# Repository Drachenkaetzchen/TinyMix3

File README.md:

# TinyMix3

TinyMix3 is a very small, 3 channel stereo audio mixer for your pocket. It features touch and USB control and is meant
to be powered by USB. 

## Features

- Very low power consumption (<50mA). Can be powered by an USB Power Bank
- USB powered
- Touch control
- USB control (presented as serial interface to the host)

## Purpose

You can use TinyMix3 to:

- Automate 3 channel stereo mixing
- Mix 3 stereo channels on the go, ideal for musicians who don't want to carry around bulky mixers

## Usage

Manual mixing

- Connect your inputs and your output
- Touch the "CH" button to switch between the three input channels. The selected channel is indicated via the LEDs.
- After a second, TinyMix3 indicates the volume for the selected channel
- You can then use the + and - touch buttons to adjust the volume
- After 10 seconds, the LEDs turn off to save power

Automatic mixing

- Connect to the TinyMix3 using a serial terminal
- TBD: Which commands the TinyMix3 supports

## Design

Heart of the TinyMix3 is the TDA7448. It is a 6 channel mono / 3 channel stereo mixer controlled via I²C. For combining
the 3 stereo channels into a single stereo output, the TS912 rail-to-rail OpAmp is used. The main logic is implemented
using an Atmega8, which uses V-USB to provide USB control. It also implements the touch interface and controls the LEDs
on the front panel.

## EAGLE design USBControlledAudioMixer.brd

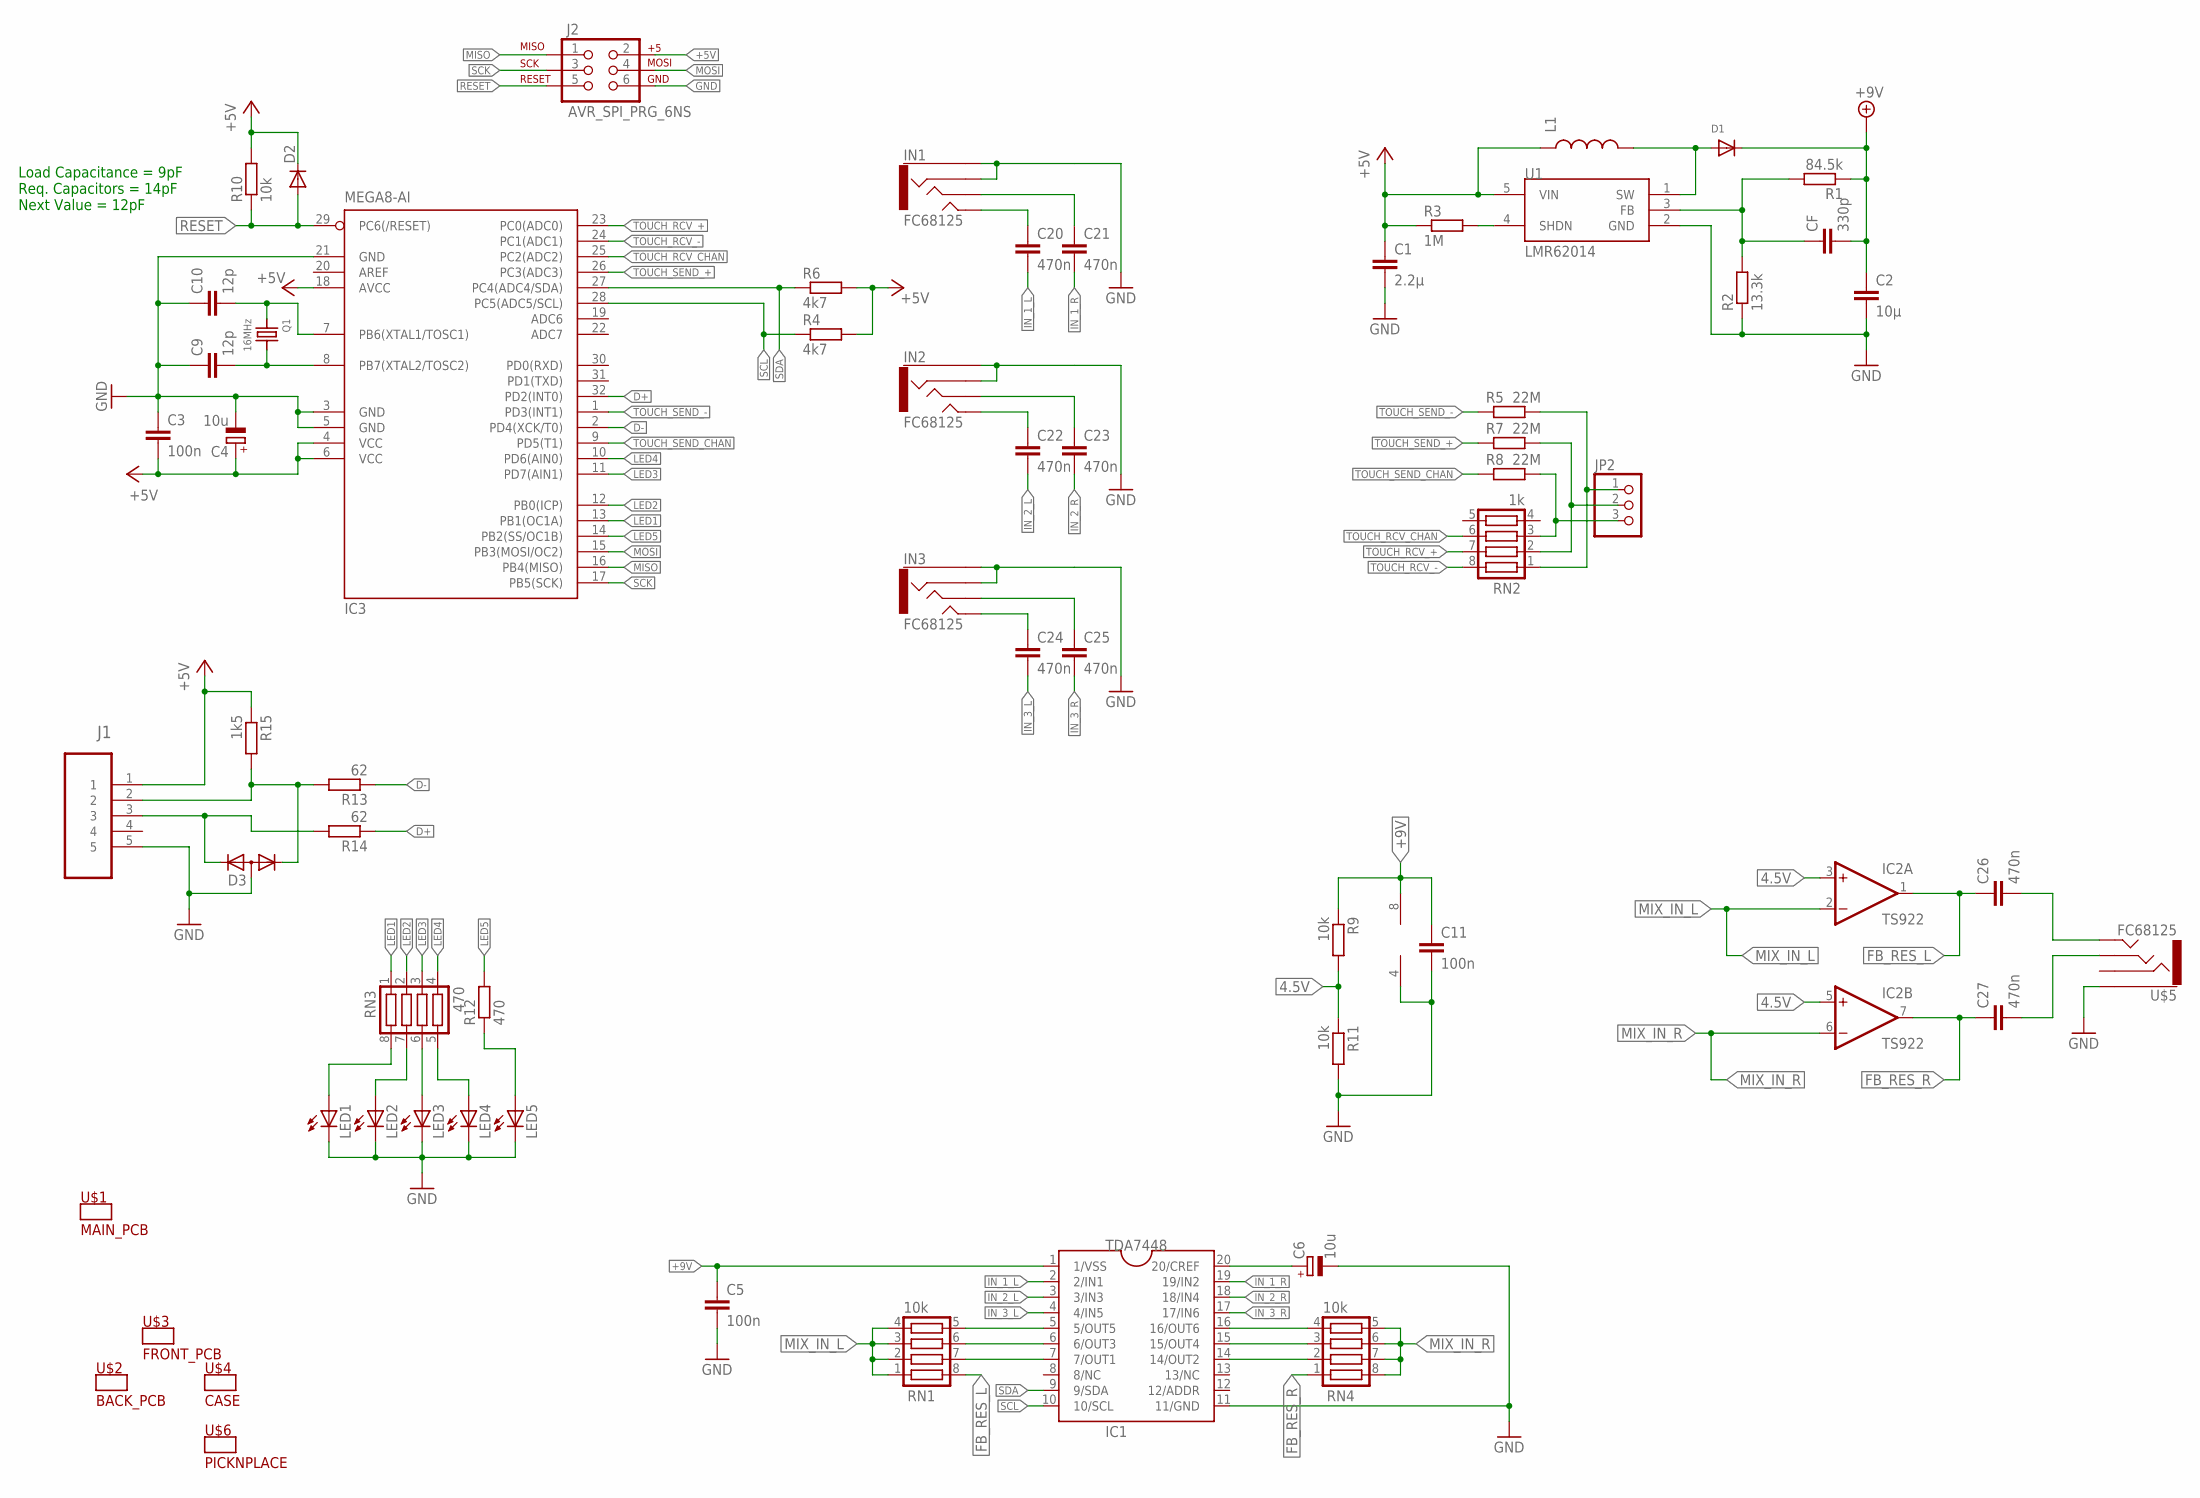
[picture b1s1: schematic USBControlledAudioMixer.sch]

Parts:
C1: 2.2µ; C0603
C2: 10µ; C0805
C3, C5, C11: 100n; C0603
C4, C6: 10u; SMC_A
C9, C10: 12p; C0603
C20, C21, C22, C23, C24, C25, C26, C27: 470n; C1206
CF: 330p; C0603
D1: DIODESOD-123; SOD-123
D2: DIODE-SOD323-R; SOD323-R
D3: DIODE-2CA|ACSOT23; SOT23
IC1: TDA7448; SO20
IC2: TS922; SO08
IC3: MEGA8-AI; TQFP32-08
IN1, IN2, IN3: FC68125
J1: 47346-0001; MOLEX_47346-0001
J2: AVR_SPI_PRG_6NS; 2X3-NS
JP2: PINHD-1X3; 1X03/90_MOLEX_4094
L1: INDUCTOR1007; 1007
LED1, LED2, LED3, LED4, LED5: LED0603; LED-0603
Q1: 16MHz; CRYSTAL_3.2X2.5
R1: 84.5k; R0603
R2: 13.3k; R0603
R3: 1M; R0603
R4, R6: 4k7; R0603
R5, R7, R8: 22M; R0603
R9, R10, R11: 10k; R0603
R12: 470; R0603
R13, R14: 62; R0603
R15: 1k5; R0603
RN1, RN4: 10k; YC164
RN2: 1k; YC164
RN3: 470; YC164
U1: LMR62014; SOT-23
U$5: FC68125

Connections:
4.5V: IC2.3 (+IN), IC2.5 (+IN), R9.2, R11.1
+5V: C1.1, C3.2, C4.+, D2.C, IC3.4 (VCC), IC3.6 (VCC), IC3.18 (AVCC), J1.1, J2.2, L1.1, R3.1, R4.2, R6.2, R10.2, R15.1, U1.5 (VIN)
+9V: C2.1, C5.1, C11.1, CF.2, D1.C, IC1.1 (1/VSS), IC2.8 (V+), R1.1, R9.1
D+: IC3.32 (PD2(INT0)), R14.1
D-: IC3.2 (PD4(XCK/T0)), R13.1
FB: CF.1, R1.2, R2.2, U1.3 (FB)
FB_RES_L: C26.1, IC2.1 (OUT), RN1.8
FB_RES_R: C27.1, IC2.7 (OUT), RN4.1
GND: C1.2, C2.2, C3.1, C4.-, C5.2, C6.-, C9.1, C10.1, C11.2, D3.3 (A), IC1.11 (11/GND), IC2.4 (V-), IC3.3 (GND), IC3.5 (GND), IC3.21 (GND), IN1.1, IN1.6 (2), IN2.1, IN2.6 (2), IN3.1, IN3.6 (2), J1.5, J2.6, LED1.C, LED2.C, LED3.C, LED4.C, LED5.C, R2.1, R11.2, U1.2 (GND), U$5.1
IN_1_L: C20.2, IC1.2 (2/IN1)
IN_1_R: C21.2, IC1.19 (19/IN2)
IN_2_L: C22.2, IC1.3 (3/IN3)
IN_2_R: C23.2, IC1.18 (18/IN4)
IN_3_L: C24.2, IC1.4 (4/IN5)
IN_3_R: C25.2, IC1.17 (17/IN6)
LED1: IC3.13 (PB1(OC1A)), RN3.1
LED2: IC3.12 (PB0(ICP)), RN3.2
LED3: IC3.11 (PD7(AIN1)), RN3.3
LED4: IC3.10 (PD6(AIN0)), RN3.4
LED5: IC3.14 (PB2(SS/OC1B)), R12.2
MISO: IC3.16 (PB4(MISO)), J2.1
MIX_IN_L: IC2.2 (-IN), RN1.1, RN1.2, RN1.3, RN1.4
MIX_IN_R: IC2.6 (-IN), RN4.5, RN4.6, RN4.7, RN4.8
MOSI: IC3.15 (PB3(MOSI/OC2)), J2.4
unnamed: C6.+, IC1.20 (20/CREF)
unnamed: C9.2, IC3.8 (PB7(XTAL2/TOSC2)), Q1.2
unnamed: C10.2, IC3.7 (PB6(XTAL1/TOSC1)), Q1.1
unnamed: LED1.A, RN3.8
unnamed: LED2.A, RN3.7
unnamed: LED3.A, RN3.6
unnamed: LED4.A, RN3.5
unnamed: LED5.A, R12.1
unnamed: C24.1, IN3.2 (4)
unnamed: D3.1 (K1), J1.2, R13.2, R15.2
unnamed: C25.1, IN3.3, IN3.3A (3)
unnamed: D3.2 (K2), J1.3, R14.2
unnamed: C22.1, IN2.2 (4)
unnamed: C23.1, IN2.3, IN2.3A (3)
unnamed: C20.1, IN1.2 (4)
unnamed: C21.1, IN1.3, IN1.3A (3)
unnamed: JP2.1, R5.2, RN2.1
unnamed: JP2.2, R7.2, RN2.2
unnamed: JP2.3, R8.2, RN2.3
unnamed: IC1.5 (5/OUT5), RN1.5
unnamed: IC1.6 (6/OUT3), RN1.6
unnamed: C26.2, U$5.2 (4)
unnamed: IC1.7 (7/OUT1), RN1.7
unnamed: C27.2, U$5.3, U$5.3A (3)
unnamed: IC1.16 (16/OUT6), RN4.4
unnamed: IC1.15 (15/OUT4), RN4.3
unnamed: IC1.14 (14/OUT2), RN4.2
RESET: D2.A, IC3.29 (PC6(/RESET)), J2.5, R10.1
SCK: IC3.17 (PB5(SCK)), J2.3
SCL: IC1.10 (10/SCL), IC3.28 (PC5(ADC5/SCL)), R4.1
SDA: IC1.9 (9/SDA), IC3.27 (PC4(ADC4/SDA)), R6.1
SHDN: R3.2, U1.4 (SHDN)
SW: D1.A, L1.2, U1.1 (SW)
TOUCH_RCV_+: IC3.23 (PC0(ADC0)), RN2.7
TOUCH_RCV_-: IC3.24 (PC1(ADC1)), RN2.8
TOUCH_RCV_CHAN: IC3.25 (PC2(ADC2)), RN2.6
TOUCH_SEND_+: IC3.26 (PC3(ADC3)), R7.1
TOUCH_SEND_-: IC3.1 (PD3(INT1)), R5.1
TOUCH_SEND_CHAN: IC3.9 (PD5(T1)), R8.1

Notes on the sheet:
Load Capacitance = 9pF Req. Capacitors = 14pF Next Value = 12pF

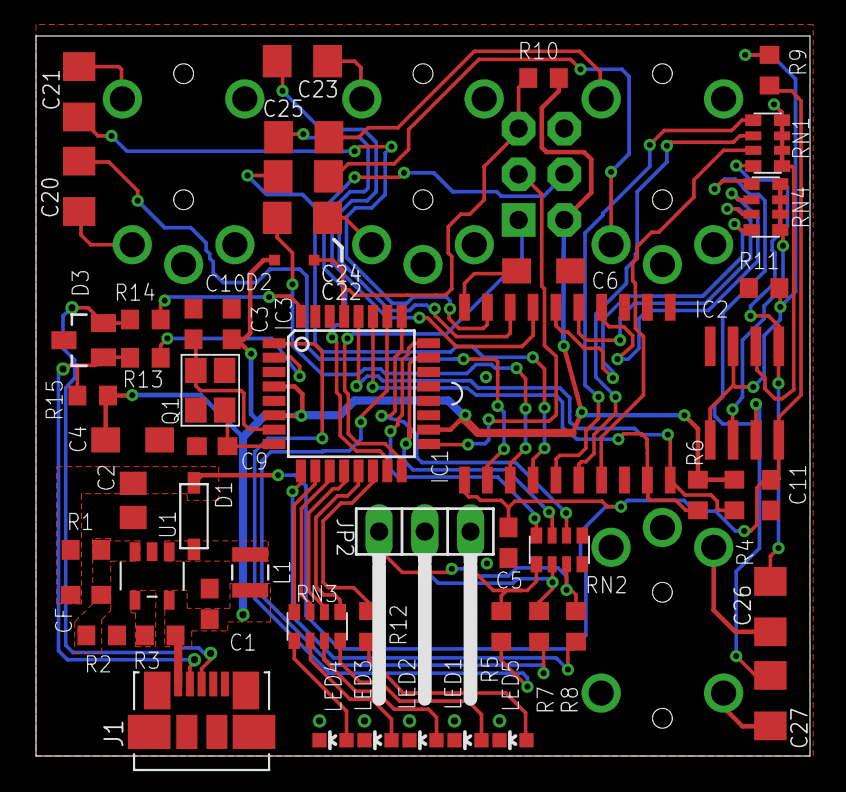
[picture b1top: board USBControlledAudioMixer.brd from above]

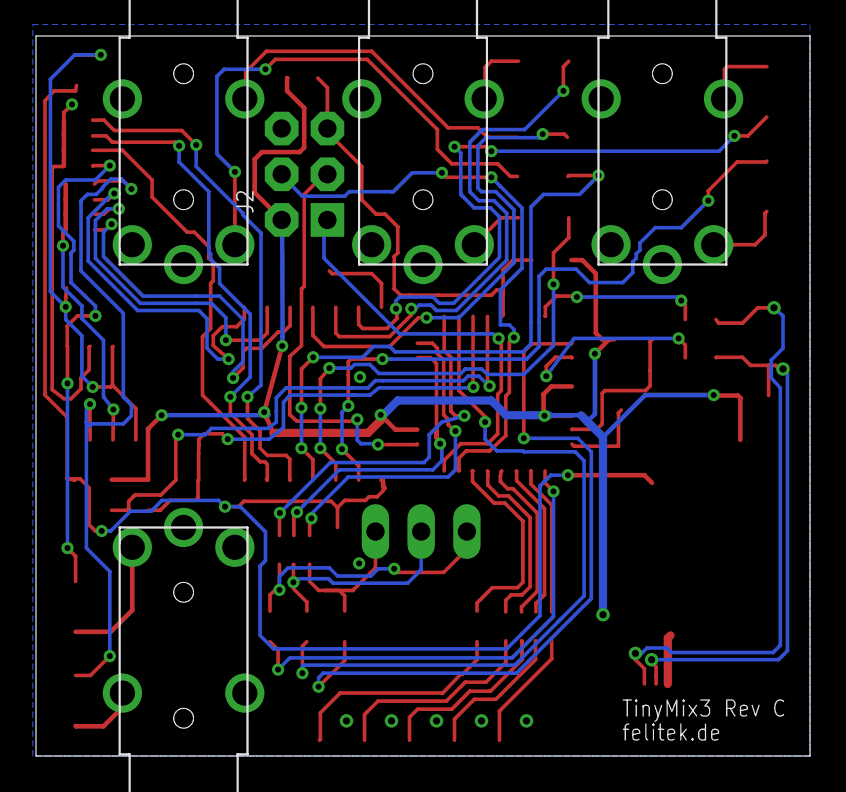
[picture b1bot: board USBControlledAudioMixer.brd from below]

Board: 2 copper layers, 43.0 x 40.0 mm, 58 parts (5 on the bottom side), 63 nets.

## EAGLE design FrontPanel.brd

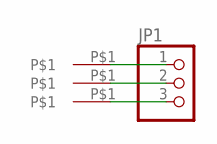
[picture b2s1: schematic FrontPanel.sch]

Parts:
JP1: PINHD-1X3_2.54-SMD; 1X03SMD
U$8, U$9, U$10: TOUCHPAD; TOUCH_FIELD_10X5

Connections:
unnamed: JP1.1, U$8.P$1
unnamed: JP1.2, U$9.P$1
unnamed: JP1.3, U$10.P$1

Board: 2 copper layers, 11 parts (1 on the bottom side), 3 nets.

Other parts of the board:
U$1: FC68125-FP
U$2, U$3, U$4, U$5, U$6: SMDLED_RIGHTANGLE0602
U$7: SMD-USB-PANEL

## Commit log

2015-04-20 Minor update (sorry for nonsense commit message)
2015-04-23 Added LEDs an basic wiring
2015-04-23 Pre-final version without proper board layout
2015-04-25 Routing done, silkscreen adjustments missing
2015-04-27 Initial front panel design
2015-05-01 Remove eagle.epf, added evie
2015-05-01 Refactored whole board because due to case layout constraint, the regular through-hole film capacitors couldn't be used anymore. We're now using 1206 SMD film capacitors.
2015-05-03 Semi-finalized board, front and back panel Added 100nF capacitor for the TDA7448 mixer
2015-05-03 Added readme
2015-05-05 Fixed hole sizes
2015-05-07 Added ESD protection for the RESET line
2015-05-20 Fixed hole size, use smaller connector for the front panel
2016-03-15 Added progress report
2016-03-15 Added info regarding cables
2016-03-16 updated progress
2016-03-16 Fixed capacitor order number
2016-03-16 Corrected revision number
2016-04-16 Fixed audio mixing
2016-04-16 Routed new mixer
2016-04-16 Fixed component labels

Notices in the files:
parts and their libraries:
SparkFun: Licensing: CC v3.0 Share-Alike You are welcome to use this library for commercial purposes.
